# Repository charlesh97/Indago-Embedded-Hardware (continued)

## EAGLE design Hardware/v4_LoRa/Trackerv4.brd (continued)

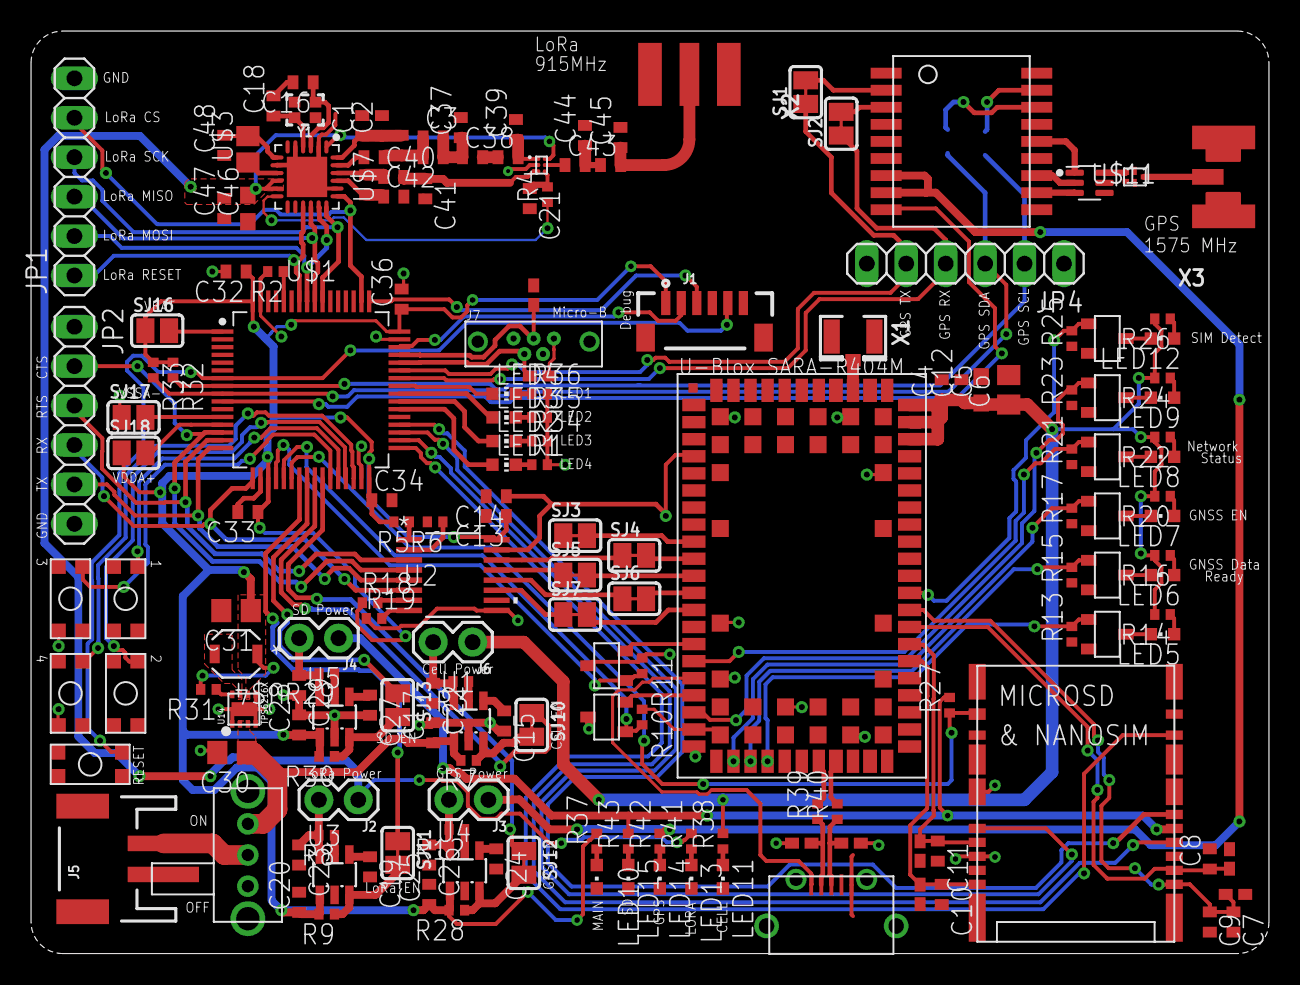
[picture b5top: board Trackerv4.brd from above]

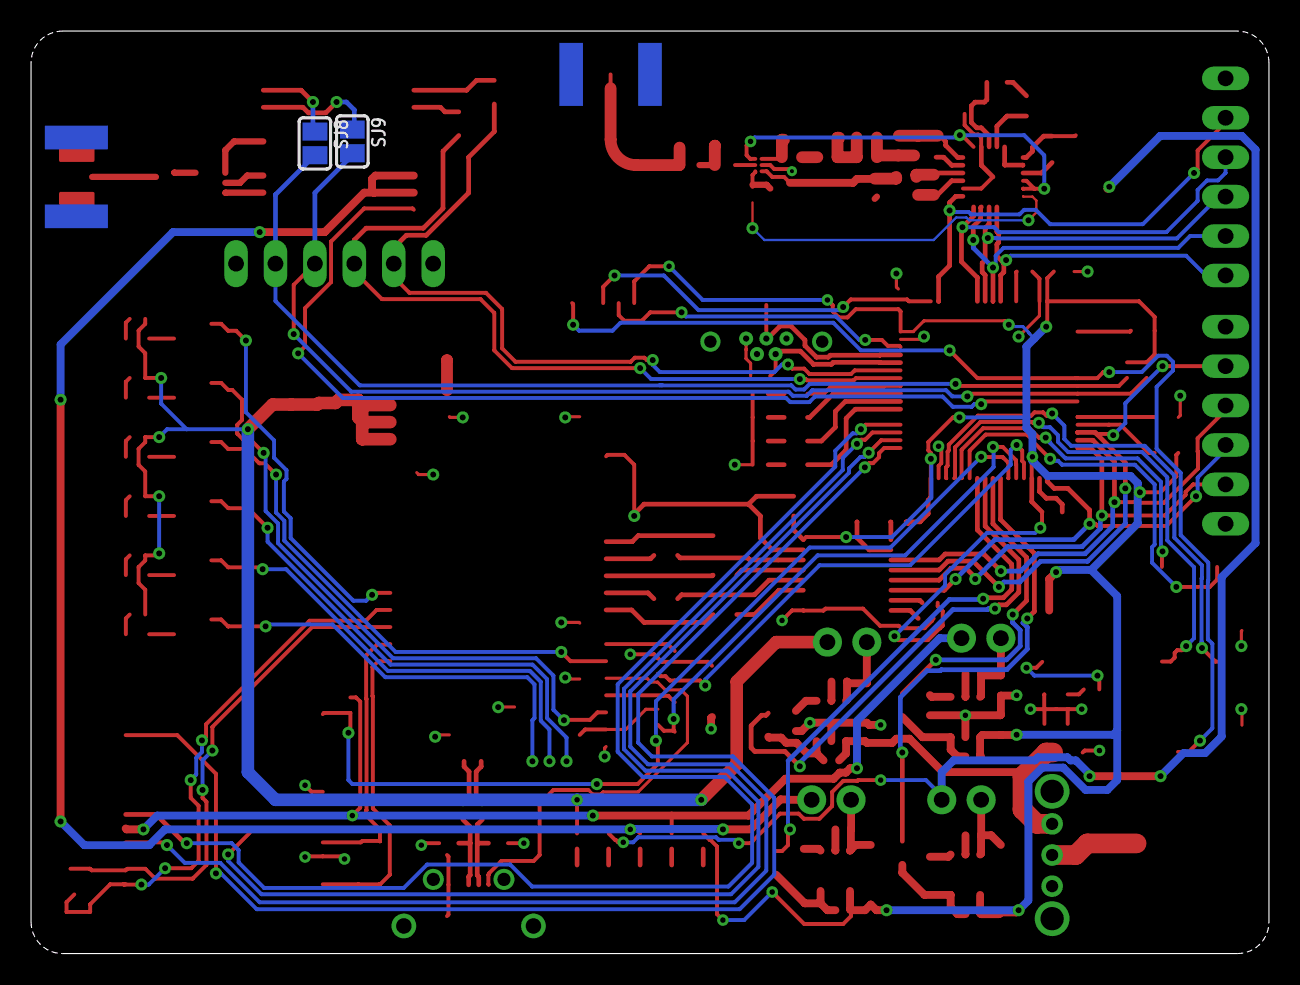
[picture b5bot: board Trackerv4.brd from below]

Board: 2 copper layers, 79.8 x 59.4 mm, 180 parts (2 on the bottom side), 147 nets.

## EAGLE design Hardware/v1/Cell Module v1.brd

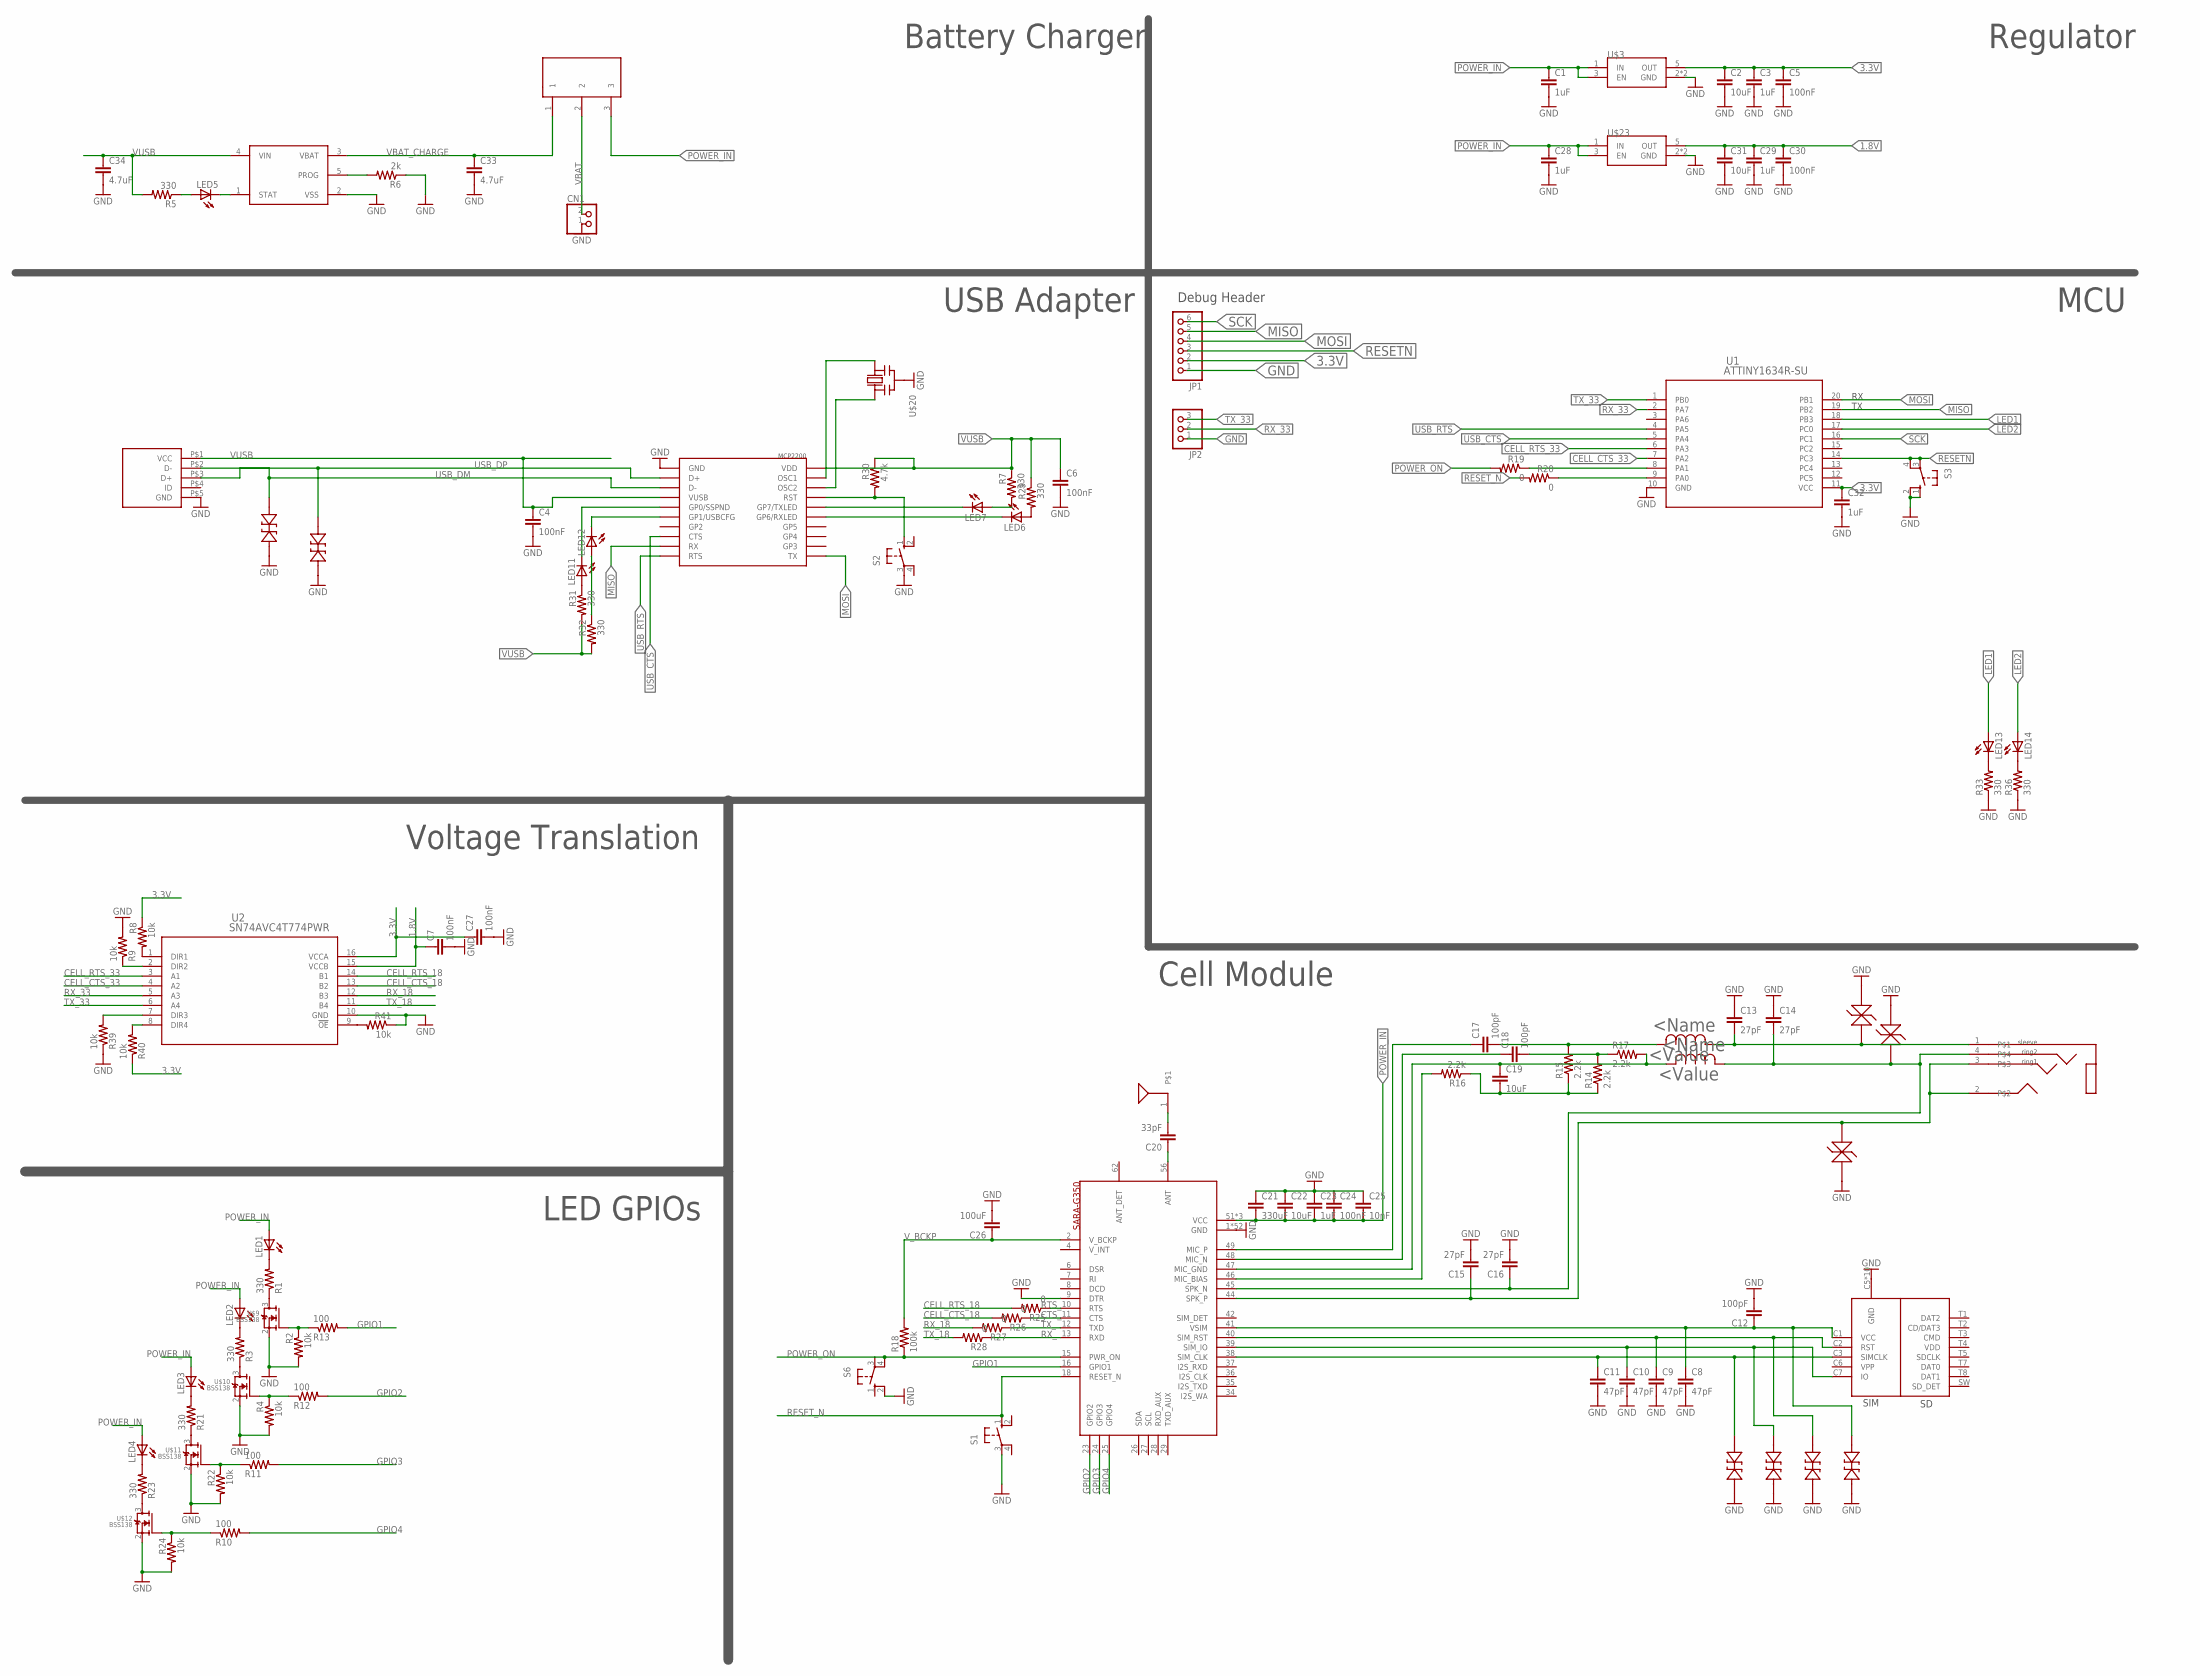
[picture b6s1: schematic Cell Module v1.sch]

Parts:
C1, C3, C23, C28, C29, C32: 1uF; C0402
C2, C19, C22, C31: 10uF; C0603
C4, C5, C6, C7, C24, C27, C30: 100nF; C0402
C8, C9, C10, C11: 47pF; C0402
C12, C17, C18: 100pF; C0402
C13, C14, C15, C16: 27pF; C0402
C20: 33pF; C0402
C21: 330uF; C1210
C25: 10nF; C0402
C26: 100uF; C1206
C33, C34: 4.7uF; C0402
CN1: JST_2PIN-THM; JST-PH-2-THM
CR1, CR2, CR3, CR4, CR5, CR6: PESD0402-140; PESD0402
JP1: PINHD-1X6; 1X06
JP2: PINHD-1X3; 1X03
LED1, LED2, LED3, LED4, LED6, LED7, LED11, LED12, LED13, LED14: LEDCHIP-LED0805; CHIP-LED0805
LED5: LEDCHIP-LED0603; CHIP-LED0603
R1, R3, R5, R7, R21, R23, R29, R31, R32, R33, R36: 330; R0402
R2, R4, R8, R9, R22, R24, R39, R40, R41: 10k; R0402
R6: 2k; R0402
R10, R11, R12, R13: 100; R0402
R14, R15, R16, R17: 2.2k; R0402
R18: 100k; R0402
R19, R20, R25, R26, R27, R28: 0; R0402
R30: 4.7k; R0402
S1, S2, S3, S6: 10-XX; B3F-10XX
U1: ATTINY1634R-SU; 20S2
U2: SN74AVC4T774PWR; PW16
U$1: SARA-G350
U$2: SIM_SD_MOLEX
U$3, U$23: TPS782XX; SOT23-5L
U$4: MCP73831; SOT23-5L
U$5: MICRO_USB; MOLEX_USB
U$6: SPDT_THRU
U$7: A10340
U$8: SJ-43514-SMT-TR
U$9, U$10, U$11, U$12: BSS138; SOT23-3
U$13, U$14: LQG15HS82NJ02; 0402
U$16, U$17, U$18: CG0402MLE-18G; 0402
U$19: MCP2200; SOIC20_65PITCH_LARGER
U$20: CERMOSCILL-AWCSR; AWCSR

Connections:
1.8V: C7.1, C29.1, C30.1, C31.1, U2.15 (VCCB), U$23.5 (OUT)
3.3V: C2.1, C3.1, C5.1, C27.1, C32.1, JP1.2, R8.1, R40.1, U1.11 (VCC), U2.16 (VCCA), U$3.5 (OUT)
CELL_CTS_18: R26.2, U2.13 (B2)
CELL_CTS_33: U1.7 (PA2), U2.4 (A2)
CELL_RTS_18: R25.2, U2.14 (B1)
CELL_RTS_33: U1.6 (PA3), U2.3 (A1)
CTS_: R26.1, U$1.11 (CTS)
GND: C1.2, C2.2, C3.2, C4.2, C5.2, C6.2, C7.2, C8.2, C9.2, C10.2, C11.2, C12.2, C13.1, C14.1, C15.2, C16.2, C21.1, C22.1, C23.1, C24.1, C25.1, C26.2, C27.2, C28.2, C29.2, C30.2, C31.2, C32.2, C33.2, C34.2, CN1.1 (2), CR1.1 (11), CR2.1 (11), CR3.1 (11), CR4.1 (11), CR5.1 (11), CR6.1 (11), JP1.1, JP2.1, R2.2, R4.2, R6.1, R9.2, R22.2, R24.2, R33.1, R36.1, R39.1, R41.1, S1.3, S2.3, S3.1 (S), S3.2 (S1), S6.2 (S1), U1.10 (GND), U2.10 (GND), U$1.1 (GND), U$1.3 (GND), U$1.5 (GND), U$1.9 (DTR), U$1.14 (GND), U$1.20 (GND), U$1.21 (GND), U$1.22 (GND), U$1.30 (GND), U$1.32 (GND), U$1.43 (GND), U$1.50 (GND), U$1.54 (GND), U$1.55 (GND), U$1.57 (GND), U$1.58 (GND), U$1.59 (GND), U$1.60 (GND), U$1.61 (GND), U$1.63 (GND), U$1.64 (GND), U$1.65 (GND), U$1.66 (GND), U$1.67 (GND), U$1.68 (GND), U$1.69 (GND), U$1.70 (GND), U$1.71 (GND), U$1.72 (GND), U$1.73 (GND), U$1.74 (GND), U$1.75 (GND), U$1.76 (GND), U$1.77 (GND), U$1.78 (GND), U$1.79 (GND), U$1.80 (GND), U$1.81 (GND), U$1.82 (GND), U$1.83 (GND), U$1.84 (GND), U$1.85 (GND), U$1.86 (GND), U$1.87 (GND), U$1.88 (GND), U$1.89 (GND), U$1.90 (GND), U$1.91 (GND), U$1.92 (GND), U$1.93 (GND), U$1.94 (GND), U$1.95 (GND), U$1.96 (GND), U$2.C5 (GND), U$2.G1 (GND), U$2.G2 (GND), U$2.G3 (GND), U$2.G4 (GND), U$2.G5 (GND), U$2.G6 (GND), U$2.G7 (GND), U$2.G8 (GND), U$2.T6 (GND), U$3.2 (GND), U$3.4 (GND), U$4.2 (VSS), U$5.P$5 (GND), U$9.2 (S), U$10.2 (S), U$11.2 (S), U$12.2 (S), U$16.2, U$17.1, U$18.1, U$19.20 (GND), U$20.2 (GND), U$23.2 (GND), U$23.4 (GND)
GPIO1: R13.2, U$1.16 (GPIO1)
GPIO2: R12.2, U$1.23 (GPIO2)
GPIO3: R11.2, U$1.24 (GPIO3)
GPIO4: R10.2, U$1.25 (GPIO4)
LED1: LED13.A, U1.18 (PB3)
LED2: LED14.A, U1.17 (PC0)
MISO: JP1.5, U1.19 (PB2), U$19.12 (RX)
MOSI: JP1.4, U1.20 (PB1), U$19.10 (TX)
unnamed: LED7.C, U$19.5 (GP7/TXLED)
unnamed: LED6.C, U$19.6 (GP6/RXLED)
unnamed: LED5.C, U$4.1 (STAT)
unnamed: LED5.A, R5.1
unnamed: LED1.C, R1.2
unnamed: R6.2, U$4.5 (PROG)
unnamed: LED7.A, R7.2
unnamed: C11.1, CR1.2 (22), U$1.38 (SIM_CLK), U$2.C3 (SIMCLK)
unnamed: R1.1, U$9.3 (D)
unnamed: R8.2, U2.1 (DIR1)
unnamed: R9.1, U2.2 (DIR2)
unnamed: LED6.A, R29.2
unnamed: LED2.C, R3.2
unnamed: R3.1, U$10.3 (D)
unnamed: U$19.2 (OSC1), U$20.3 (OUT)
unnamed: U$19.3 (OSC2), U$20.1 (IN)
unnamed: LED3.C, R21.2
unnamed: C10.1, CR2.2 (22), U$1.39 (SIM_IO), U$2.C7 (IO)
unnamed: C9.1, CR3.2 (22), U$1.40 (SIM_RST), U$2.C2 (RST)
unnamed: C8.1, C12.1, CR4.2 (22), U$1.41 (VSIM), U$2.C1 (VCC)
unnamed: R16.2, U$1.46 (MIC_BIAS)
unnamed: C18.1, U$1.48 (MIC_N)
unnamed: C17.1, U$1.49 (MIC_P)
unnamed: C19.2, R14.1, R15.1, R16.1
unnamed: C19.1, R17.2, U$1.47 (MIC_GND), U$14.2
unnamed: C18.2, R14.2, R17.1
unnamed: C17.2, R15.2, U$13.2
unnamed: C13.2, U$8.1, U$13.1, U$18.2
unnamed: C14.2, C16.1, U$1.45 (SPK_N), U$8.4, U$14.1, U$17.2
unnamed: C15.1, U$1.44 (SPK_P), U$8.2, U$8.3, U$16.1
unnamed: C20.1, U$1.56 (ANT)
unnamed: C20.2, U$7.1
unnamed: R30.2, S2.1 (S), U$19.4 (RST)
unnamed: LED11.C, U$19.16 (GP0/SSPND)
unnamed: LED12.C, U$19.15 (GP1/USBCFG)
unnamed: LED11.A, R31.1
unnamed: LED12.A, R32.1
unnamed: R21.1, U$11.3 (D)
unnamed: R19.1, U1.8 (PA1)
unnamed: LED4.C, R23.2
unnamed: R23.1, U$12.3 (D)
unnamed: R20.1, U1.9 (PA0)
unnamed: LED13.C, R33.2
unnamed: LED14.C, R36.2
unnamed: R2.1, R13.1, U$9.1 (G)
unnamed: R4.1, R12.1, U$10.1 (G)
unnamed: R40.2, U2.8 (DIR4)
unnamed: R39.2, U2.7 (DIR3)
unnamed: R41.2, U2.9 (!OE)
unnamed: R11.1, R22.1, U$11.1 (G)
unnamed: R10.1, R24.1, U$12.1 (G)
POWER_IN: C1.1, C21.2, C22.2, C23.2, C24.2, C25.2, C28.1, LED1.A, LED2.A, LED3.A, LED4.A, U$1.51 (VCC), U$1.52 (VCC), U$1.53 (VCC), U$3.1 (IN), U$3.3 (EN), U$6.3, U$23.1 (IN), U$23.3 (EN)
POWER_ON: R18.1, R19.2, S6.3, S6.4 (P1), U$1.15 (PWR_ON)
RESETN: JP1.3, S3.3, S3.4 (P1), U1.14 (PC3)
RESET_N: R20.2, S1.1 (S), U$1.18 (RESET_N)
RTS_: R25.1, U$1.10 (RTS)
RX_: R28.1, U$1.13 (RXD)
RX_18: R27.2, U2.12 (B3)
RX_33: JP2.2, U1.2 (PA7), U2.5 (A3)
SCK: JP1.6, U1.16 (PC1)
TX_: R27.1, U$1.12 (TXD)
TX_18: R28.2, U2.11 (B4)
TX_33: JP2.3, U1.1 (PB0), U2.6 (A4)
USB_CTS: U1.5 (PA4), U$19.13 (CTS)
USB_DM: CR5.2 (22), U$5.P$2 (D-), U$19.18 (D-)
USB_DP: CR6.2 (22), U$5.P$3 (D+), U$19.19 (D+)
USB_RTS: U1.4 (PA5), U$19.11 (RTS)
VBAT: CN1.2 (1), U$6.2
VBAT_CHARGE: C33.1, U$4.3 (VBAT), U$6.1
VUSB: C4.1, C6.1, C34.1, R5.2, R7.1, R29.1, R30.1, R31.2, R32.2, U$4.4 (VIN), U$5.P$1 (VCC), U$19.1 (VDD), U$19.17 (VUSB)
V_BCKP: C26.1, R18.2, U$1.2 (V_BCKP)

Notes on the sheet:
Cell Module
USB Adapter
Battery Charger
Regulator
MCU
Debug Header
Voltage Translation
LED GPIOs

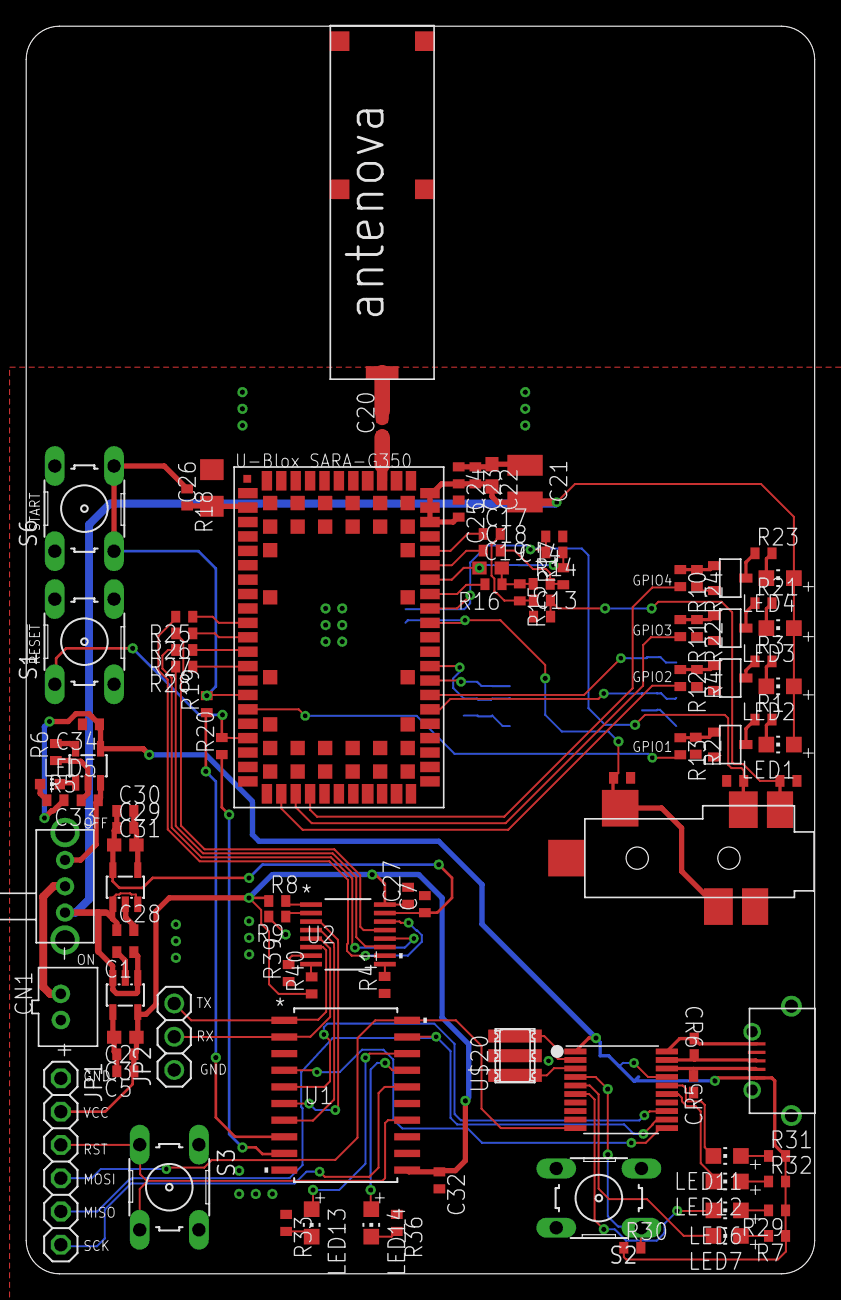
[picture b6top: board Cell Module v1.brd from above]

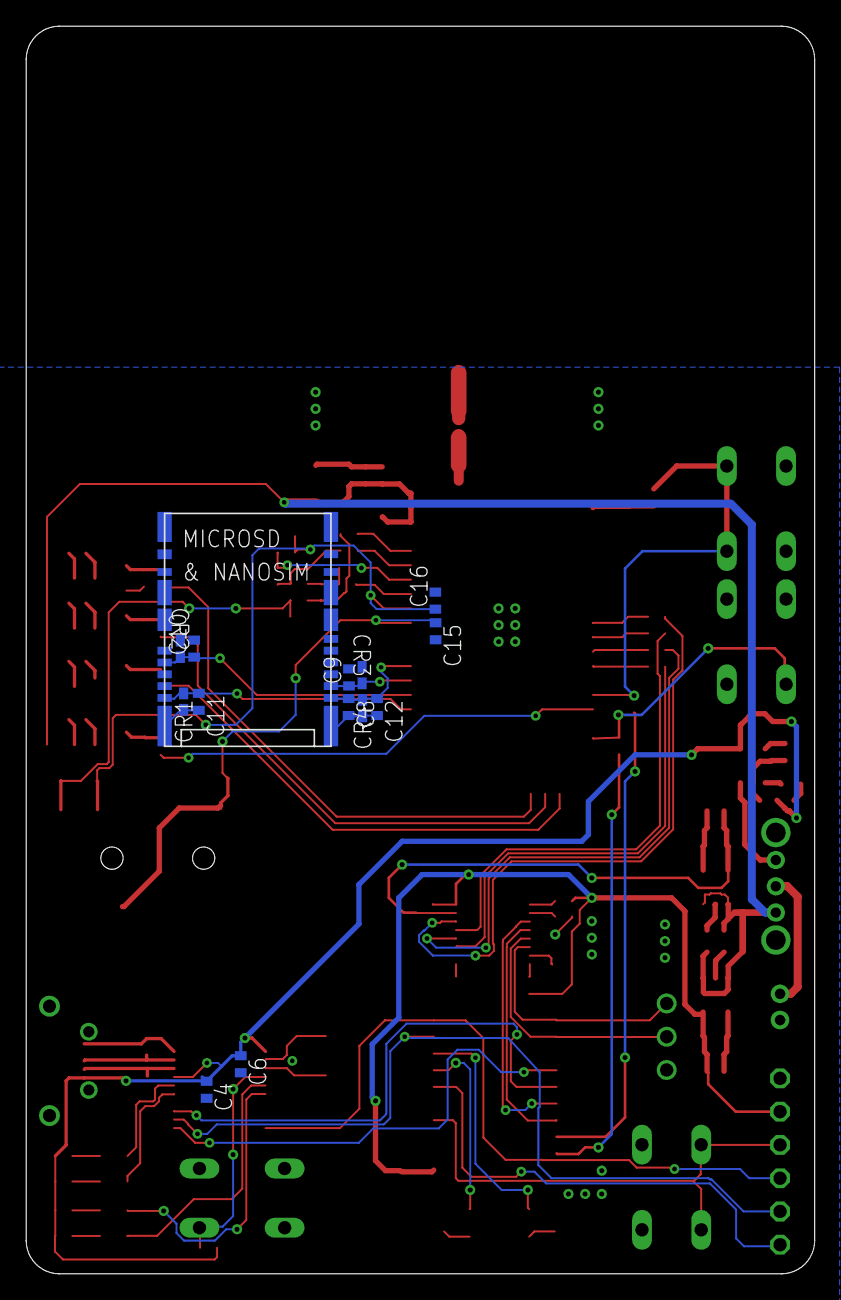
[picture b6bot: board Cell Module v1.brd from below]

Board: 2 copper layers, 60.2 x 95.2 mm, 117 parts (14 on the bottom side), 87 nets.

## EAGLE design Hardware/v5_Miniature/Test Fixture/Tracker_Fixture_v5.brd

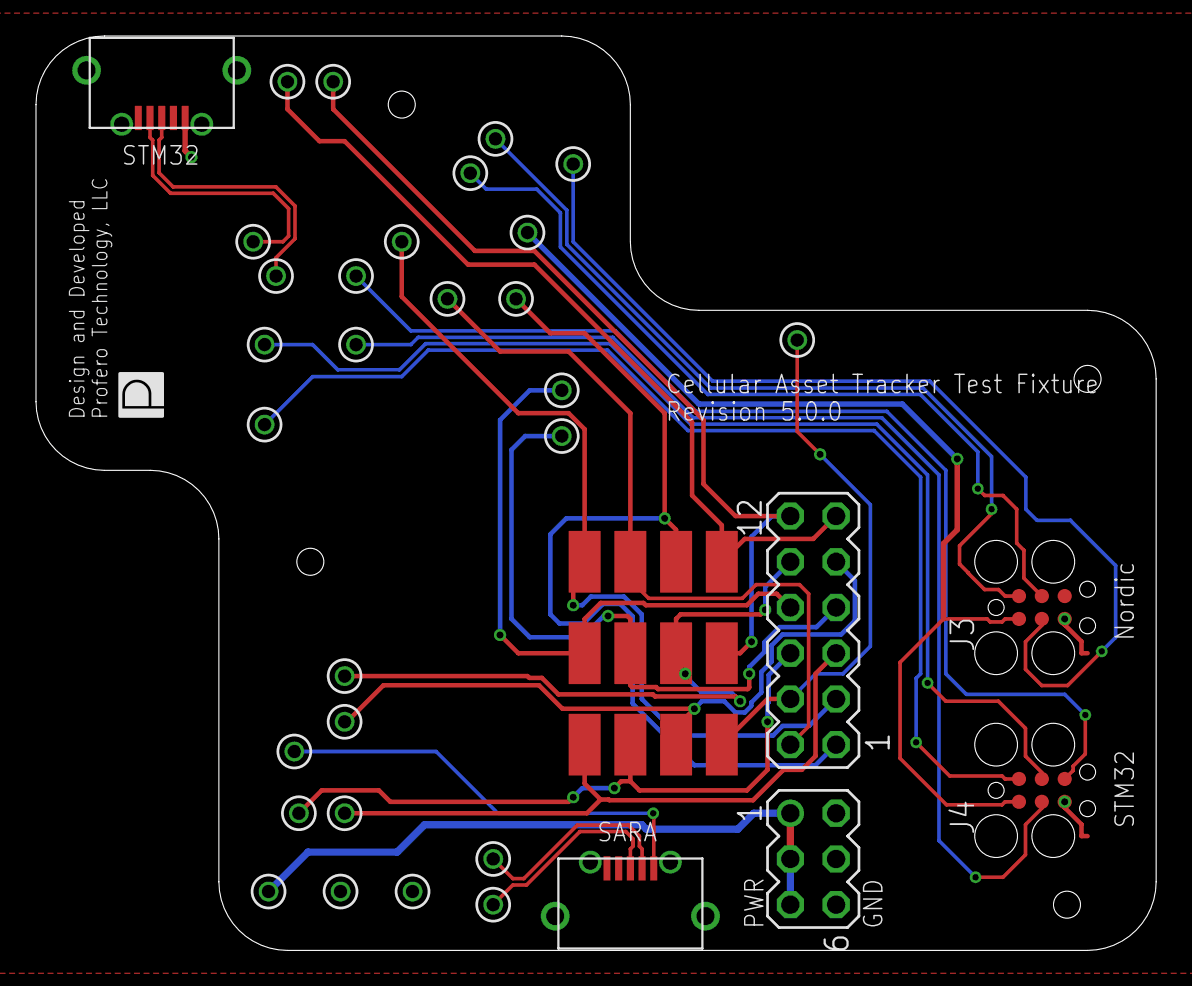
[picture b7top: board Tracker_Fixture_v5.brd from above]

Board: 2 copper layers, 62.2 x 50.8 mm, 47 parts (0 on the bottom side), 27 nets.

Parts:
J1, J2: MICRO_USB047590; MOLEX_USB_047590
J3, J4: TC2030-MCP
SV1: MA06-2
SV2: MA03-2
TP1, TP2, TP3, TP4, TP5, TP6, TP7, TP8, TP9, TP10, TP11, TP12, TP13, TP14, TP15, TP16, TP17, TP18, TP19, TP20, TP21, TP22, TP23, TP24, TP25, TP26, TP39, TP40: 0914-X-15-20-77-14-11-0; MILLMAX-0914-X
TP27, TP28, TP29, TP30, TP31, TP32, TP33, TP34, TP35, TP36, TP37, TP38: 5017; KEYSTONE-5017
U$1: PROFERO-LOGO-SMALL

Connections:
EINK_CS: SV1.3, TP16.1, TP29.P$1
EINK_MOSI: SV1.1, TP18.1, TP31.P$1
EINK_SCK: SV1.2, TP17.1, TP30.P$1
GND: J1.5, J2.5, J3.5, J4.5, SV2.2, SV2.4, SV2.6, TP2.1, TP3.1
GPS_RX: SV1.7, TP25.1, TP33.P$1
GPS_SCL: SV1.5, TP7.1, TP35.P$1
GPS_SDA: SV1.6, TP6.1, TP34.P$1
GPS_TX: SV1.8, TP24.1, TP32.P$1
ISP_RESET: J3.3, TP21.1
ISP_SWCLK: J3.4, TP19.1
ISP_SWDIO: J3.2, TP20.1
PACK+: SV2.1, SV2.3, SV2.5, TP1.1
SARA_D_N: J2.2, TP5.1
SARA_D_P: J2.3, TP4.1
SARA_RX: SV1.9, TP9.1, TP38.P$1
SARA_TX: SV1.10, TP8.1, TP37.P$1
SARA_USB_DET: J2.1, TP39.1
SCL: SV1.11, TP22.1, TP27.P$1
SDA: SV1.12, TP23.1, TP28.P$1
ST_RESET: J4.3, TP13.1
ST_SWCLK: J4.4, TP12.1
ST_SWDIO: J4.2, TP14.1
ST_SWO: J4.6, TP15.1
TIMEPULSE: SV1.4, TP26.1, TP36.P$1
USB_D_N: J1.2, TP10.1
USB_D_P: J1.3, TP11.1
VDDIO: J3.1, J4.1, TP40.1

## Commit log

2022-02-05 Configure SAST in `.gitlab-ci.yml`, creating this file if it does not already exist
2022-02-05 Pushing all old files from Google Drive
2022-02-06 Adding files
